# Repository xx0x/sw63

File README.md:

# Space Watch SW63

Sci-fi inspired electronic watch.

*MK4 in the development, out in 2026.*

## How to tell the time?

When the button is briefly pressed, SW63 tells you the time using a sequence of LED blinks. It's not a binary clock, it's inspired by the analog clock hands movement and uses quarters, halves and so on; similar to how people used to tell the time before the digital clock became popular.
  
**16:35**  
*half past - four - hours - and - five - minutes - PM*

**6:57**  
*three - minutes - to - whole - seven - hours*

Language can be changed in the watch menu to reflect the different ways different languages express the time ("half past five" in English is "half of six" in German etc).

See [LANGUAGES.md](./LANGUAGES.md) for the full list and examples.

## Controls

**Short press:** Show the time  
**Long press:** Enter Menu (setting the language and time)  
**Extra long press:** Enter Secret settings  
**Multiple short presses:** Show animation

*In Menu / Secret settings:*  
**Short press:** Change  
**Long press:** Confirm and go to next

## BOM (DIY Kits)

| Name                                | Part Number                                   | Qty |
| ----------------------------------- | --------------------------------------------- | --- |
| PCB with assembled SMD components   | custom part                                   | 1   |
| Red 5 mm LED                        | LL-503VD2E-V1-4D                              | 1   |
| Green 5 mm LED                      | LL-504PGD2E-G5-2B                             | 1   |
| Blue 5 mm LED                       | LL-504BD2E-B4-2B                              | 1   |
| Yellow 5 mm LED                     | N0Y64L35<br> L-53SYD<br> L-53SYDK             | 1   |
| Yellow 3×2 mm LED                   | LL-234YD2Q-1B                                 | 4   |
| Red 3 mm LED                        | FYL-3014LRD1A<br> FYL-3014SRT1A               | 1   |
| Li-Po battery LP301020 or LP301120* | AKY0471<br> SparkFun 13852<br> SparkFun 25270 | 1   |
| CNC aluminium enclosure             | custom part                                   | 1   |
| Screw M1.6 length 4mm (hex socket)  | -                                             | 4   |
| 18 mm watch spring bar              | -                                             | 2   |
| 18 mm watch strap                   | -                                             | 1   |

> [!WARNING]
> \***Note:** Due to the shipping restrictions the Li-Po battery isn't part of the DIY Kit. Please provide your own 40 mAh battery with dimensions 20 mm × 11 mm × 3 mm (or smaller) with the integrated protection circuit.

## License

**Schematics, Hardware Designs**  
CERN-OHL-P-2.0

**Code**  
MIT

**Visual elements, Graphics, Documentation**  
CC BY-SA 4.0

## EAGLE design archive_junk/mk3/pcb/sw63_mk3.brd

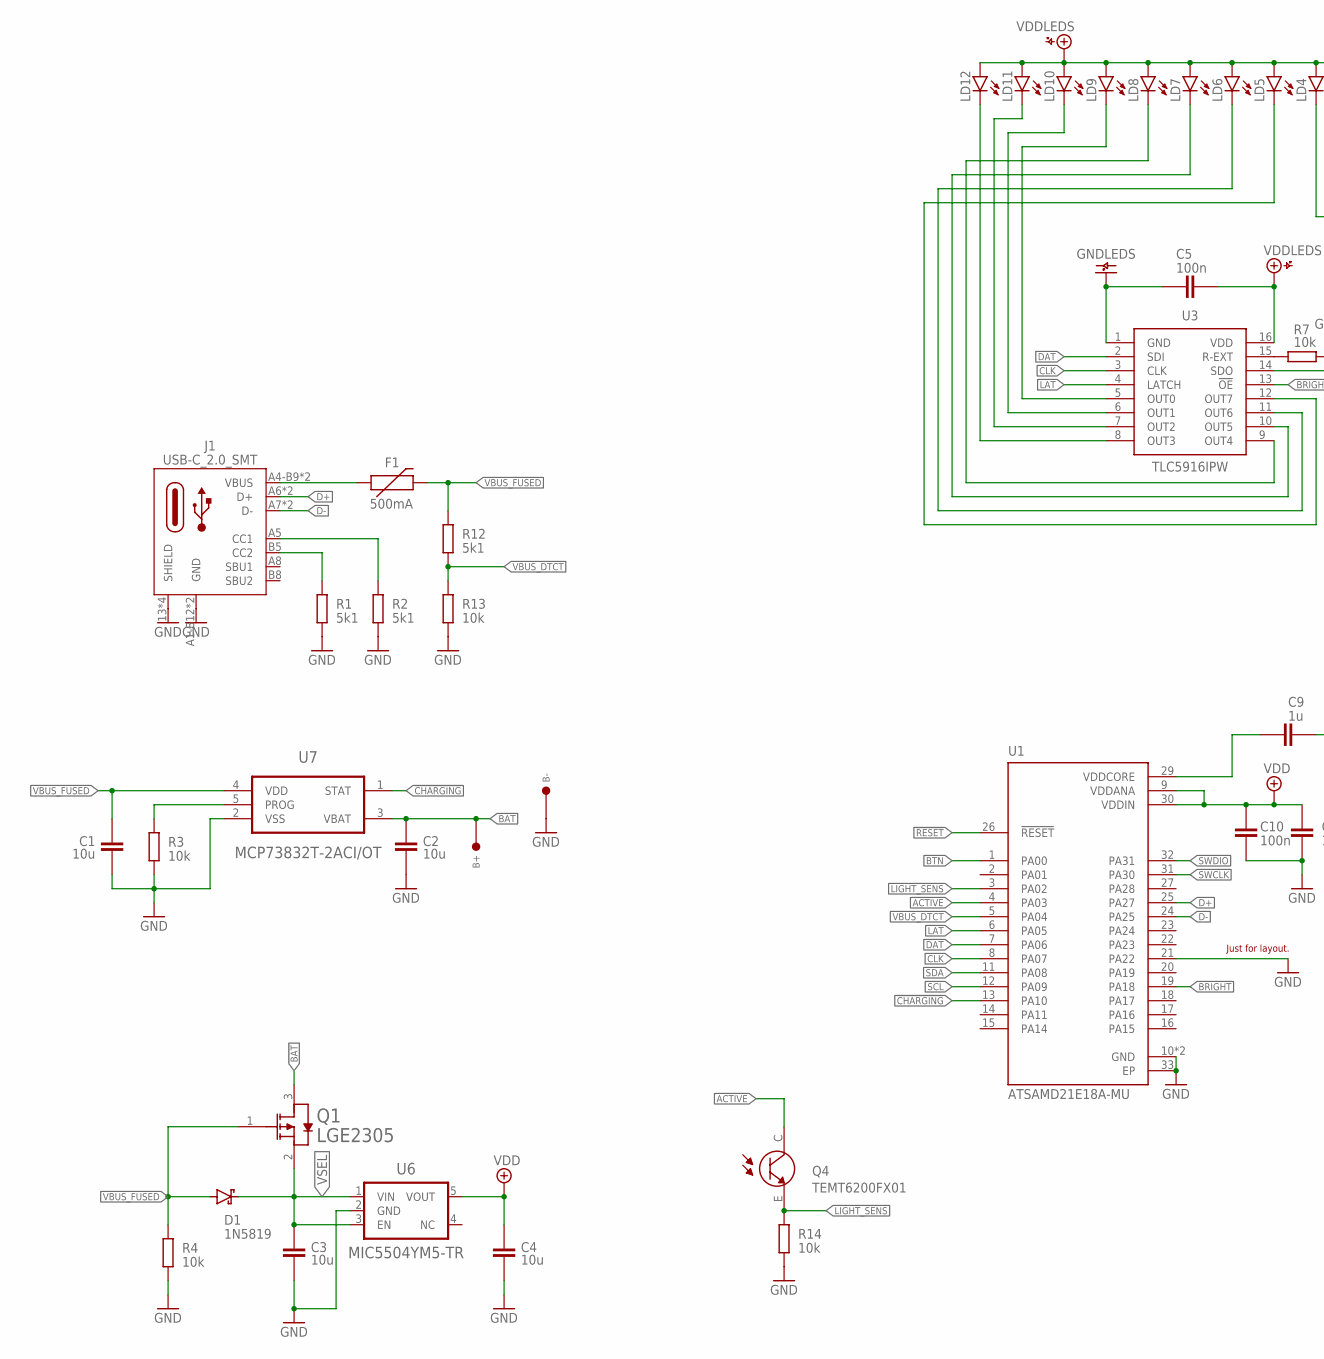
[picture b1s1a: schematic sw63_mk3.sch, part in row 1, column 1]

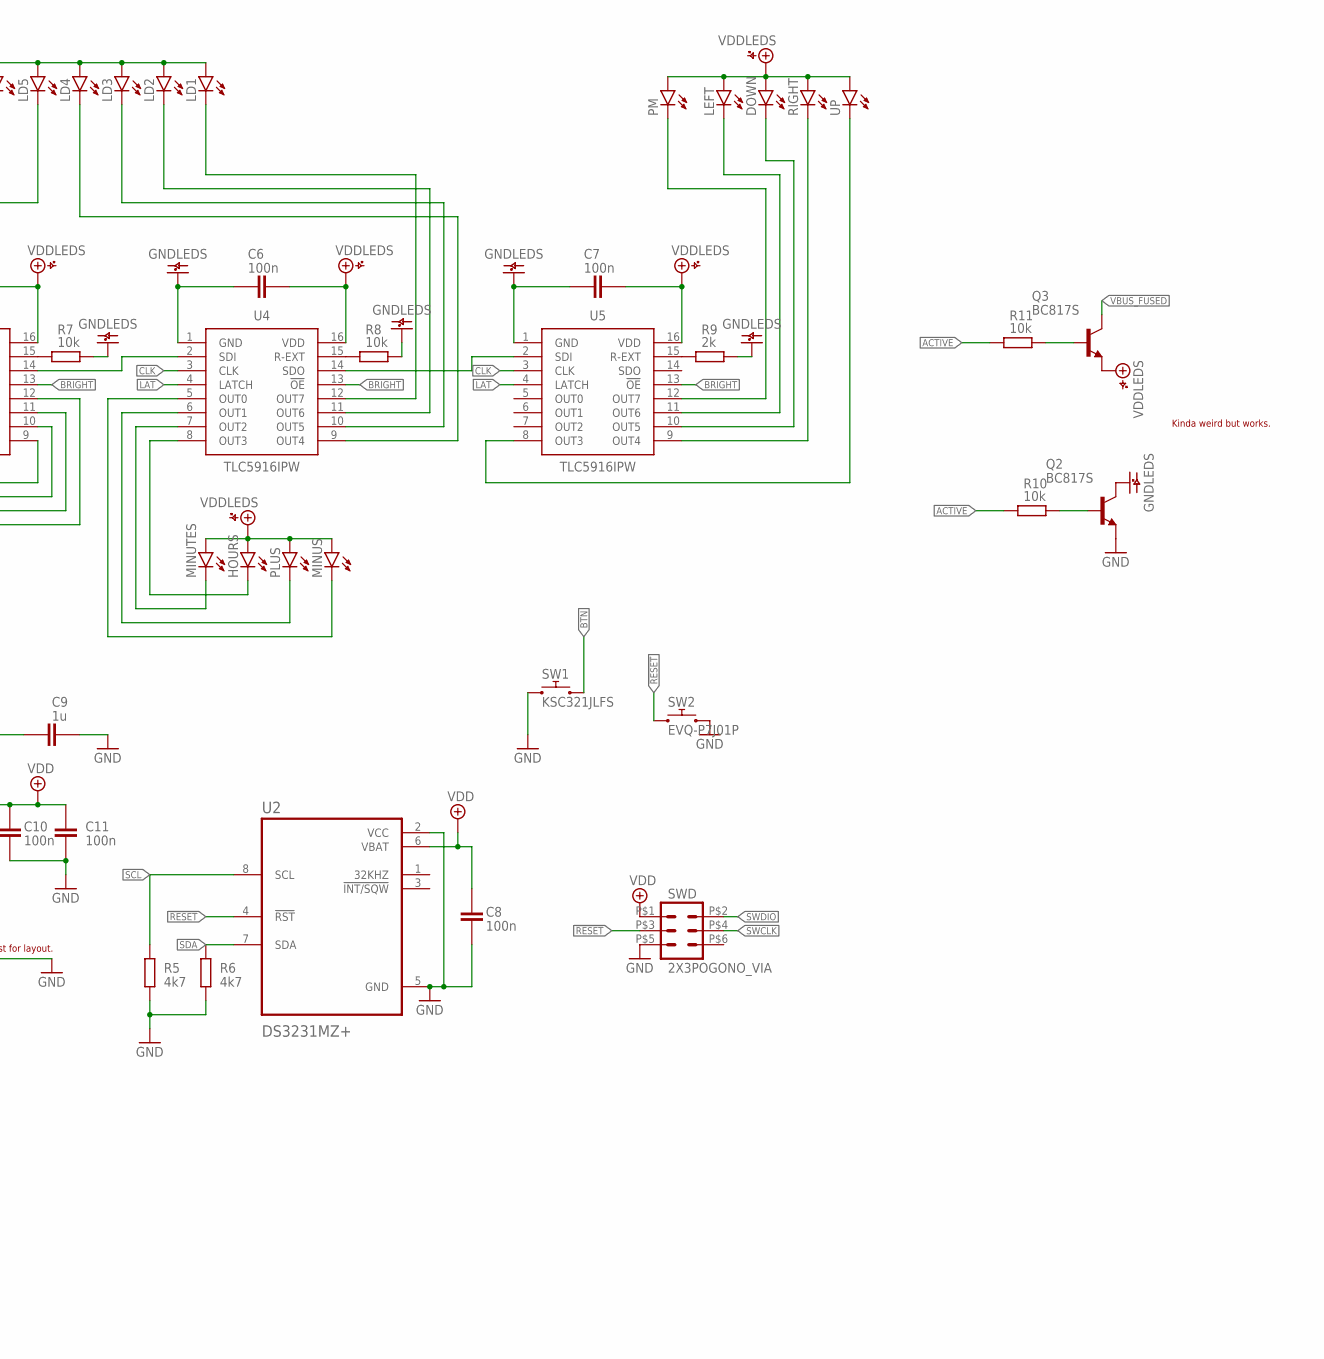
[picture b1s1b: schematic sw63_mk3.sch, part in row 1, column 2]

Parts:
B+: TEST_PIN_LARGE; TEST_PIN_2.0
B-: TEST_PIN_LARGE; TEST_PIN_2.0
C1, C2, C3, C4: 10u; CAPACITOR0805
C5, C6, C7, C8, C10, C11: 100n; CAPACITOR0603
C9: 1u; CAPACITOR0603
D1: 1N5819; SOD123
DOWN: LED_RECT-3.2X2; LED_RECT_3.2X2
F1: 500mA; PTC0805
HOURS: LED_THT-5MM_B; LED_5MM_BLUE
J1: USB-C_2.0_SMT; USB-C_FULL_SMT
LD1, LD2, LD3, LD4, LD5, LD6, LD7, LD8, LD9, LD10, LD11, LD12: LED_SMT_1206; LED_1206
LEFT: LED_RECT-3.2X2; LED_RECT_3.2X2
MINUS: LED_THT-5MM_R; LED_5MM_RED
MINUTES: LED_THT-5MM_Y; LED_5MM_YELLOW
PLUS: LED_THT-5MM_G; LED_5MM_GREEN
PM: LED_THT-3MM_ALT; LED_3MM_ALT
Q1: LGE2305; SOT23
Q2, Q3: BC817S; SOT23
Q4: TEMT6200FX01
R1, R2, R12: 5k1; RESISTOR0603
R3, R4, R7, R8, R10, R11, R13, R14: 10k; RESISTOR0603
R5, R6: 4k7; RESISTOR0603
R9: 2k; RESISTOR0603
RIGHT: LED_RECT-3.2X2; LED_RECT_3.2X2
SW1: KSC321JLFS; KSC3XXJ
SW2: EVQ-P7J01P
SWD: 2X3POGONO_VIA; 2X3_POGO_NO_VIA
U1: ATSAMD21E18A-MU; QFN50P500X500X100-33N
U2: DS3231MZ+; SO8
U3, U4, U5: TLC5916IPW; TSSOP16
U6: MIC5504YM5-TR; SOT23-5
U7: MCP73832T-2ACI/OT; SOT23-5
UP: LED_RECT-3.2X2; LED_RECT_3.2X2

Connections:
!CHARGING: U1.13 (PA10), U7.1 (STAT)
!RESET: SW2.1_1 (1), SW2.1_2 (1), SWD.P$3 (3), U1.26 (!RESET), U2.4 (!RST)
ACTIVE: Q4.C, R10.2, R11.2, U1.4 (PA03)
BAT: B+.P$1, C2.1, Q1.3 (DRAIN), U7.3 (VBAT)
BRIGHT: U1.19 (PA18), U3.13 (!OE), U4.13 (!OE), U5.13 (!OE)
BTN: SW1.2, SW1.4 (2), U1.1 (PA00)
CLK: U1.8 (PA07), U3.3 (CLK), U4.3 (CLK), U5.3 (CLK)
D+: J1.A6 (D+), J1.B6 (D+), U1.25 (PA27)
D-: J1.A7 (D-), J1.B7 (D-), U1.24 (PA25)
DAT: U1.7 (PA06), U3.2 (SDI)
GND: B-.P$1, C1.2, C2.2, C3.2, C4.2, C8.2, C9.1, C10.1, C11.1, J1.13 (SHIELD), J1.14 (SHIELD), J1.15 (SHIELD), J1.16 (SHIELD), J1.A1-B12 (GND), J1.B1-A12 (GND), Q2.2 (E), R1.1, R2.1, R3.1, R4.1, R5.1, R6.1, R13.1, R14.1, SW1.1, SW1.3 (1), SW2.2_1 (2), SW2.2_2 (2), SWD.P$5 (5), U1.10 (GND), U1.21 (PA22), U1.28 (GND), U1.33 (EP), U2.2 (VCC), U2.5 (GND), U6.2 (GND), U7.2 (VSS)
GNDLEDS: C5.1, C6.1, C7.1, Q2.3 (C), R7.1, R8.1, R9.1, U3.1 (GND), U4.1 (GND), U5.1 (GND)
LAT: U1.6 (PA05), U3.4 (LATCH), U4.4 (LATCH), U5.4 (LATCH)
LIGHT_SENS: Q4.E, R14.2, U1.3 (PA02)
unnamed: F1.2 (1), J1.A4-B9 (VBUS), J1.B4-A9 (VBUS)
unnamed: J1.B5 (CC2), R1.2
unnamed: J1.A5 (CC1), R2.2
unnamed: R3.2, U7.5 (PROG)
unnamed: LD12.C, U3.8 (OUT3)
unnamed: LD11.C, U3.7 (OUT2)
unnamed: R7.2, U3.15 (R-EXT)
unnamed: R8.2, U4.15 (R-EXT)
unnamed: R9.2, U5.15 (R-EXT)
unnamed: Q2.1 (B), R10.1
unnamed: U4.14 (SDO), U5.2 (SDI)
unnamed: U3.14 (SDO), U4.2 (SDI)
unnamed: Q3.1 (B), R11.1
unnamed: PM.K (C), U5.12 (OUT7)
unnamed: DOWN.K (C), U5.10 (OUT5)
unnamed: LEFT.K (C), U5.11 (OUT6)
unnamed: RIGHT.K (C), U5.9 (OUT4)
unnamed: U5.8 (OUT3), UP.K (C)
unnamed: LD10.C, U3.6 (OUT1)
unnamed: LD9.C, U3.5 (OUT0)
unnamed: LD8.C, U3.9 (OUT4)
unnamed: LD7.C, U3.10 (OUT5)
unnamed: LD6.C, U3.11 (OUT6)
unnamed: LD5.C, U3.12 (OUT7)
unnamed: C9.2, U1.29 (VDDCORE)
unnamed: LD4.C, U4.9 (OUT4)
unnamed: LD3.C, U4.10 (OUT5)
unnamed: LD2.C, U4.11 (OUT6)
unnamed: LD1.C, U4.12 (OUT7)
unnamed: HOURS.K (C), U4.8 (OUT3)
unnamed: MINUTES.K (C), U4.7 (OUT2)
unnamed: PLUS.K (C), U4.6 (OUT1)
unnamed: MINUS.K (C), U4.5 (OUT0)
SCL: R5.2, U1.12 (PA09), U2.8 (SCL)
SDA: R6.2, U1.11 (PA08), U2.7 (SDA)
SWCLK: SWD.P$4 (4), U1.31 (PA30)
SWDIO: SWD.P$2 (2), U1.32 (PA31)
VBUS_DTCT: R12.1, R13.2, U1.5 (PA04)
VBUS_FUSED: C1.1, D1.A, F1.3 (2), Q1.1 (GATE), Q3.3 (C), R4.2, R12.2, U7.4 (VDD)
VDD: C4.1, C8.1, C10.2, C11.2, SWD.P$1 (1), U1.9 (VDDANA), U1.30 (VDDIN), U2.6 (VBAT), U6.5 (VOUT)
VDDLEDS: C5.2, C6.2, C7.2, DOWN.A, HOURS.A, LD1.A, LD2.A, LD3.A, LD4.A, LD5.A, LD6.A, LD7.A, LD8.A, LD9.A, LD10.A, LD11.A, LD12.A, LEFT.A, MINUS.A, MINUTES.A, PLUS.A, PM.A, Q3.2 (E), RIGHT.A, U3.16 (VDD), U4.16 (VDD), U5.16 (VDD), UP.A
VSEL: C3.1, D1.C, Q1.2 (SOURCE), U6.1 (VIN), U6.3 (EN)

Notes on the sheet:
Kinda weird but works.
Just for layout.

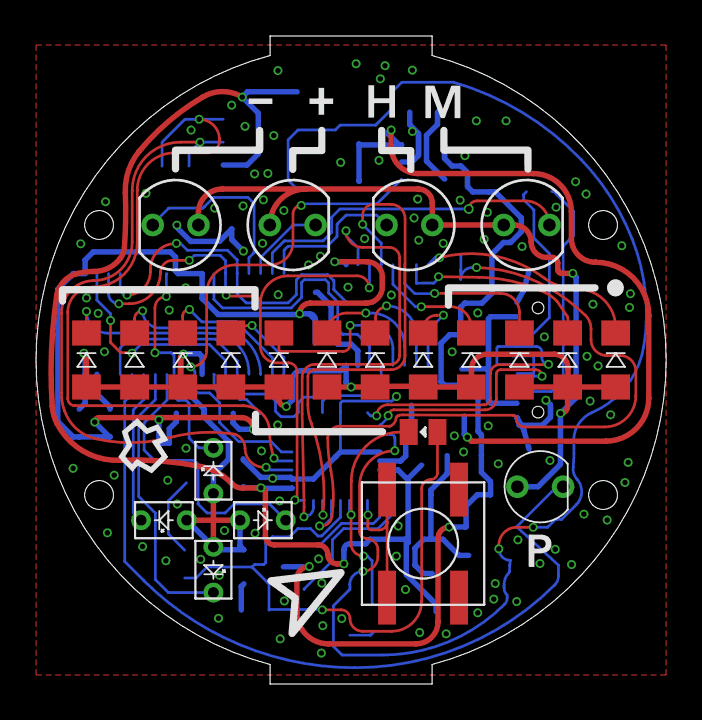
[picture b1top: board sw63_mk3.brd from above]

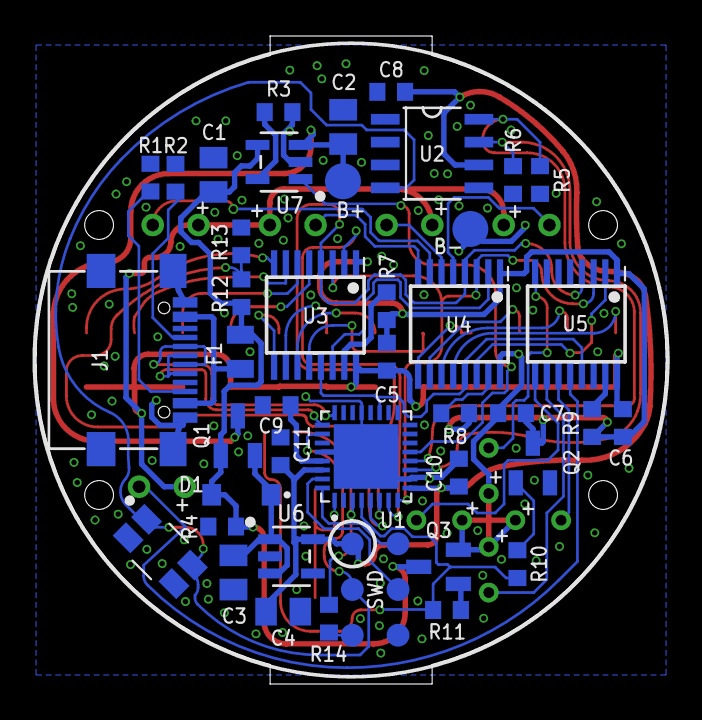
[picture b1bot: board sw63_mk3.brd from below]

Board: 2 copper layers, 35.0 x 36.0 mm, 65 parts (42 on the bottom side), 56 nets.

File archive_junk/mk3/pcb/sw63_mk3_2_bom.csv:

Comment,Designator,Footprint,LCSC Part #
,PM,LED_3MM_ALT,
,HOURS,LED_5MM_BLUE,
,PLUS,LED_5MM_GREEN,
,MINUS,LED_5MM_RED,
,MINUTES,LED_5MM_YELLOW,
1N5819,D1,SOD123,
1u,C9,CAPACITOR0603,
2X3POGONO_VIA,SWD,2X3_POGO_NO_VIA,
2k,R9,RESISTOR0603,
4k7,R5 R6,RESISTOR0603,
5k1,R1 R2 R12,RESISTOR0603,
10k,R3 R4 R7 R8 R10 R13 R14,RESISTOR0603,
10u,C1 C2 C3 C4,CAPACITOR0805,
100n,C5 C6 C7 C8 C10 C11,CAPACITOR0603,
2302,Q2,SOT23,
2305,Q1,SOT23,
ATSAMD21E18A-MU,U1,QFN50P500X500X100-33N,
BSMD0805-050-24V,F1,PTC0805,
DS3231MZ+,U2,SO8,
GT-USB-7070C,J1,USB-C_FULL_SMT_WS,
KSC321JLFS,SW1,KSC3XXJ,
LED_RECT-3.2X2,DOWN LEFT RIGHT UP,LED_RECT_3.2X2,
LED_SMT_1206,LD1 LD2 LD3 LD4 LD5 LD6 LD7 LD8 LD9 LD10 LD11 LD12,LED_1206,
MCP73832T-2ACI/OT,U7,SOT23-5,
ME6211C33M5G-N,U6,SOT23-5,
RB521S,D2 D3 D4 D5,SOD523,
SMALL_NC,SJ1,SMALL_NC_NOSILK,
TEMT6200FX01,Q4,TEMT6200FX01,
TEST_PIN_LARGE,B+ B-,TEST_PIN_2.0,
TLC5916IPW,U3 U4 U5,TSSOP16,
TSC4A 160gf-WZ 016,SW2,EVQ-P7J01P,

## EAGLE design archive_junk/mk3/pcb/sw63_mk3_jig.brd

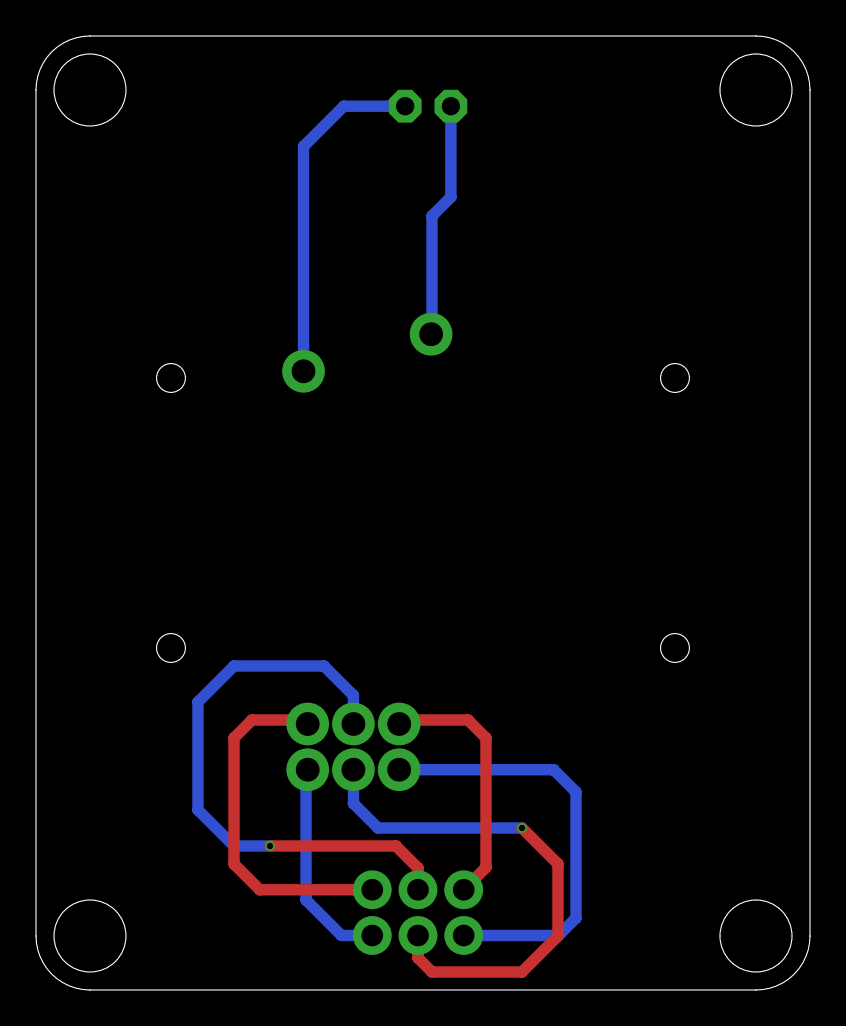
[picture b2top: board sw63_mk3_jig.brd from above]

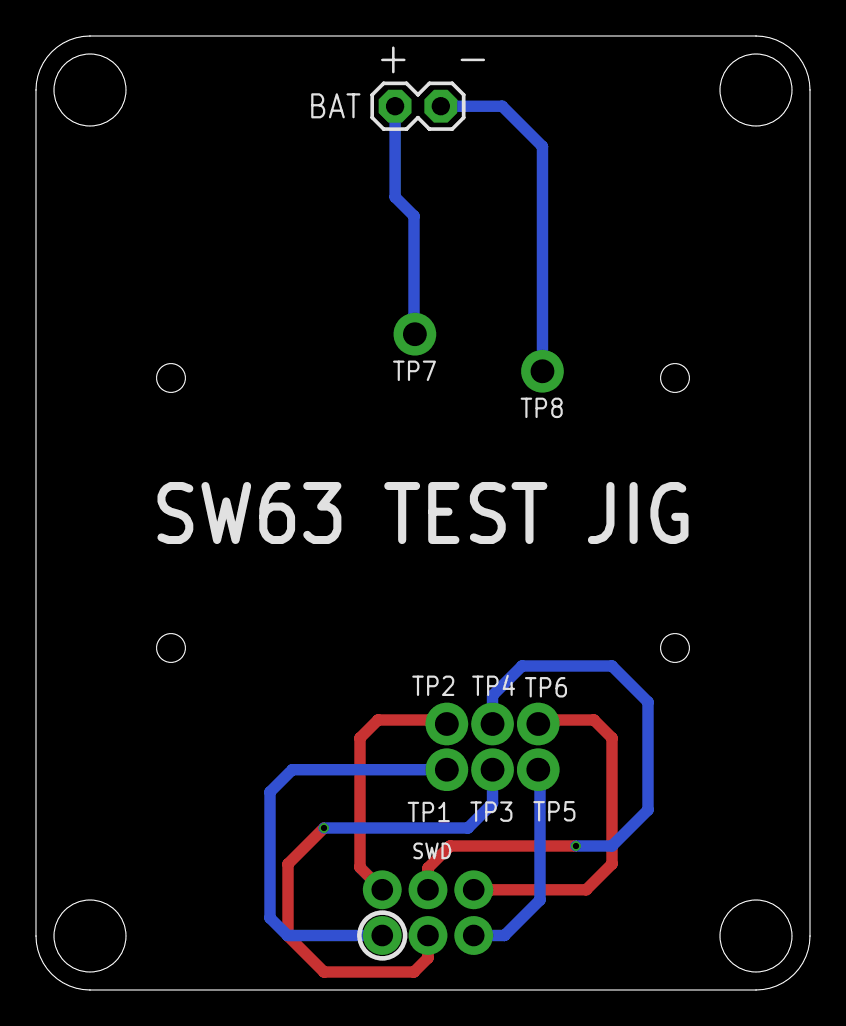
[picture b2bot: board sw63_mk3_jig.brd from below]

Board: 2 copper layers, 43.0 x 53.0 mm, 10 parts (10 on the bottom side), 8 nets.

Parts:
BAT: M02PTH; 1X02
SWD: 2X3_POGO_ROUND
TP1, TP2, TP3, TP4, TP5, TP6, TP7, TP8: R-075-SC; R-075

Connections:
BAT+: BAT.1, TP7.P$1
BAT-: BAT.2, TP8.P$1
unnamed: SWD.P$1, TP1.P$1
unnamed: SWD.P$3, TP3.P$1
unnamed: SWD.P$5, TP5.P$1
unnamed: SWD.P$6, TP6.P$1
unnamed: SWD.P$4, TP4.P$1
unnamed: SWD.P$2, TP2.P$1

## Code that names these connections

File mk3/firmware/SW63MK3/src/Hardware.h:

#ifndef SW63_HARDWARE_H
#define SW63_HARDWARE_H

#include <Arduino.h>
#include "types.h"

namespace SW63
{
    class Hardware
    {
    public:
        enum Pins
        {
            PIN_BTN,
            PIN_UNUSED1,
            PIN_LIGHT_SENS,
            PIN_ACTIVE,
            PIN_VBUS_DTCT,
            PIN_LAT,
            PIN_DAT,
            PIN_CLK,
            PIN_SDA,
            PIN_SCL,
            PIN_CHARGING,
            PIN_UNUSED2,
            PIN_UNUSED3,
            PIN_UNUSED4,
            PIN_UNUSED5,
            PIN_UNUSED6,
            PIN_BRIGHTNESS,
        };

        enum BitPositions
        {
            BP_PM,
            BP_LEFT,
            BP_DOWN,
            BP_RIGHT,
            BP_UP,
            BP_UNUSED2,
            BP_UNUSED1,
            BP_UNUSED0,
            BP_12,
            BP_11,
            BP_10,
            BP_9,
            BP_HOURS,
            BP_MINUTES,
            BP_PLUS,
            BP_MINUS,
            BP_8,
            BP_7,
            BP_6,
            BP_5,
            BP_1,
            BP_2,
            BP_3,
            BP_4,
        };

        void Init(voidFuncPtr button_callback, voidFuncPtr charge_callback);
        void SetLeds(bool minus, bool plus, bool hours, bool minutes, uint32_t digit, ClockFace face, bool pm);
        void ClearLeds();
        void TransferLeds();
        void SetActive(bool active);
        bool GetButtonState();
        void AutoBrightness();
        void Sleep();
        bool IsCharging();
        bool IsChargerConnected();

    private:
        uint32_t led_buffer_ = 0;
        void InitPins(bool init_interrupts);
        void SetBrightness(uint8_t brightness);
        uint16_t GetLightSensorValue();
    };

}

#endif

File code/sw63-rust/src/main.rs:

#![no_std]
#![no_main]

mod ds3231;

use atsamd_hal::{
    adc::{Adc, Gain, Reference, Resolution, SampleRate},
    clock::GenericClockController,
    delay::Delay,
    gpio::v2::{Pins, B, C},
    pac::{interrupt, CorePeripherals, EIC, GCLK, NVIC},
    prelude::*,
    sercom::i2c,
    target_device::Peripherals,
    time::U32Ext,
};

use cortex_m_rt::entry;
use panic_halt as _;

use ds3231::{Time, DS3231};

#[entry]
fn main() -> ! {
    // Get peripherals
    let mut peripherals = Peripherals::take().unwrap();
    let mut core = CorePeripherals::take().unwrap();

    // Configure clocks using the internal oscillator
    let mut clocks = GenericClockController::with_internal_32kosc(
        peripherals.GCLK,
        &mut peripherals.PM,
        &mut peripherals.SYSCTRL,
        &mut peripherals.NVMCTRL,
    );

    // Configure pins
    let pins = Pins::new(peripherals.PORT);

    // Configure LED on PA23 and button on PA04
    let mut led_pin = pins.pa23.into_push_pull_output();

    // Setup delay provider
    let mut delay = Delay::new(core.SYST, &mut clocks);

    // Startup indicator
    led_pin.set_high().unwrap();
    delay.delay_ms(200u32);
    led_pin.set_low().unwrap();

    // ==================================================
    // Configure GCLK with minimal power for EIC operation
    // ==================================================

    let gclk = unsafe { &*GCLK::ptr() };

    // Configure GCLK1 to use OSC32K with minimal power
    unsafe {
        // First disable the clock generator
        gclk.genctrl.write(|w| w.id().bits(1).genen().clear_bit());
        while gclk.status.read().syncbusy().bit() {}

        // Set division factor to 32 (lower power)
        gclk.gendiv.write(|w| w.id().bits(1).div().bits(32));
        while gclk.status.read().syncbusy().bit() {}

        // Configure with OSC32K and enable in standby
        gclk.genctrl.write(|w| {
            w.id().bits(1)
             .src().osc32k()
             .idc().clear_bit()    // Disable improved duty cycle (lower power)
             .genen().set_bit()
             .runstdby().set_bit() // Must run in standby for wakeup to work
        });
        while gclk.status.read().syncbusy().bit() {}

        // Connect GCLK1 to the EIC
        gclk.clkctrl.write(|w| {
            w.id().eic()
             .gen().bits(1)
             .clken().set_bit()
        });
        while gclk.status.read().syncbusy().bit() {}
    }

    // Enable EIC peripheral clock
    peripherals.PM.apbamask.modify(|_, w| w.eic_().set_bit());

    // Get EIC access
    let eic = &peripherals.EIC;

    // Disable EIC before configuring
    eic.ctrl.write(|w| w.enable().clear_bit());
    while eic.status.read().syncbusy().bit_is_set() {}

    // Configure only the button interrupt (PA04 = EXTINT[4])
    // Use input filtering to avoid spurious wakeups
    eic.config[0].write(|w| w.sense4().fall().filten4().set_bit());

    // Only enable the one interrupt we need
    eic.intenset.write(|w| w.extint4().set_bit());

    // Only enable wakeup for the specific interrupt
    eic.wakeup.write(|w| w.wakeupen4().set_bit());

    // Enable EIC
    eic.ctrl.write(|w| w.enable().set_bit());
    while eic.status.read().syncbusy().bit_is_set() {}

    // Clear any pending interrupt
    eic.intflag.write(|w| w.extint4().set_bit());

    // Configure button pin for interrupt mode
    let button_pin = pins.pa04.into_pull_up_interrupt();

    // Set up deep sleep mode
    core.SCB.set_sleepdeep();

    // Enable the EIC interrupt in NVIC
    unsafe {
        NVIC::unmask(interrupt::EIC);
    }

    // Configure I2C pins (SDA on PA08, SCL on PA09)
    // For SERCOM0, both PA08 and PA09 need to be in Alternate C mode
    let sda = pins.pa08.into_alternate::<C>();
    let scl = pins.pa09.into_alternate::<C>();

    // Set up I2C for the DS3231 RTC
    let gclk0 = clocks.gclk0();
    let sercom0_core = clocks.sercom0_core(&gclk0).unwrap();
    let i2c = i2c::I2CMaster0::new(
        &sercom0_core,
        100.khz(),
        peripherals.SERCOM0,
        &mut peripherals.PM,
        sda,
        scl,
    );

    // Create DS3231 driver
    let mut rtc = DS3231::new(i2c);

    // Set the date and time to August 18, 2025, 04:20:00
    let time = Time {
        year: 2025,
        month: 8,
        day: 18,
        hour: 4,
        minute: 20,
        second: 0,
    };

    // Set the time on the DS3231
    if let Err(_) = rtc.set_time(&time) {
        // Handle error (just blink rapidly in this example)
        loop {
            led_pin.toggle().unwrap();
            delay.delay_ms(100u32);
        }
    }

    // Configure PA02 as an analog input
    let mut analog_pin = pins.pa02.into_alternate::<B>();

    // ADC
    let mut adc = Adc::adc(peripherals.ADC, &mut peripherals.PM, &mut clocks);
    adc.reference(Reference::INTVCC1); // Internal 1/2 VDDANA reference
    adc.resolution(Resolution::_12BIT); // 12-bit resolution
    adc.samples(SampleRate::_8); // 8 samples
    adc.gain(Gain::DIV2); // 1/2 gain

    // Blink count
    let mut blink_count = 0u32;

    // Main loop
    loop {
        blink_count += 1u32;
        led_pin.toggle().unwrap();

        // Example sensor readings
        let _current_time = rtc.get_time().unwrap();
        let _brightness: u16 = adc.read(&mut analog_pin).unwrap();

        delay.delay_ms(250u32);

        // Enter deep sleep after 8 blinks
        if blink_count >= 8 {
            // Turn LED off before sleep
            led_pin.set_low().unwrap();
            blink_count = 0;

            // Disable all peripherals to save power
            disable_peripherals(&peripherals.PM);

            // Enter sleep loop - wait for any interrupt (eg. button press)
            loop {
                // Enter standby mode (deepest sleep)
                cortex_m::asm::wfi();

                // Check if button is pressed
                if button_pin.is_low().unwrap() {
                    break;
                }
            }

            // Restore peripherals
            enable_peripherals(&peripherals.PM);
        }
    }
}

#[interrupt]
fn EIC() {
    // Clear the interrupt flag in the EIC
    unsafe {
        let eic = &(*EIC::ptr());
        // Clear interrupt for EXTINT4 (button on PA04)
        eic.intflag.modify(|_, w| w.extint4().set_bit());
    }
}

fn disable_peripherals(pm: &atsamd_hal::pac::PM) {
    // AHB bus - shut down almost everything
    pm.ahbmask.write(|w| {
        w.usb_().clear_bit()
         .dmac_().clear_bit()
         .nvmctrl_().set_bit()
         .dsu_().clear_bit()
    });

    // APBA bus - keep only EIC and SYSCTRL
    pm.apbamask.write(|w| {
        w.eic_().set_bit()
         .wdt_().clear_bit()
         .sysctrl_().set_bit()
         .pac0_().clear_bit()
         .pm_().set_bit()
    });

    // APBB bus - keep only PORT
    pm.apbbmask.write(|w| {
        w.usb_().clear_bit()
         .dmac_().clear_bit()
         .nvmctrl_().clear_bit()
         .dsu_().clear_bit()
         .port_().set_bit()
         .pac1_().clear_bit()
    });

    // APBC bus - disable everything
    pm.apbcmask.write(|w| {
        w.adc_().clear_bit()
         .sercom0_().clear_bit()
         .sercom1_().clear_bit()
         .sercom2_().clear_bit()
         .sercom3_().clear_bit()
         .tcc0_().clear_bit()
         .tcc1_().clear_bit()
         .tcc2_().clear_bit()
         .tc3_().clear_bit()
         .tc4_().clear_bit()
         .tc5_().clear_bit()
         .pac2_().clear_bit()
    });
}

fn enable_peripherals(pm: &atsamd_hal::pac::PM) {
    // AHB bus - restore all peripherals
    pm.ahbmask.write(|w| {
        w.usb_().set_bit()
         .dmac_().set_bit()
         .nvmctrl_().set_bit()
         .dsu_().set_bit()
    });

    // APBA bus - restore all peripherals
    pm.apbamask.write(|w| {
        w.eic_().set_bit()
         .wdt_().set_bit()
         .sysctrl_().set_bit()
         .pac0_().set_bit()
         .pm_().set_bit()
    });

    // APBB bus - restore all peripherals
    pm.apbbmask.write(|w| {
        w.usb_().set_bit()
         .dmac_().set_bit()
         .nvmctrl_().set_bit()
         .dsu_().set_bit()
         .port_().set_bit()
         .pac1_().set_bit()
    });

    // APBC bus - restore all peripherals
    pm.apbcmask.write(|w| {
        w.adc_().set_bit()
         .sercom0_().set_bit()
         .sercom1_().set_bit()
         .sercom2_().set_bit()
         .sercom3_().set_bit()
         .tcc0_().set_bit()
         .tcc1_().set_bit()
         .tcc2_().set_bit()
         .tc3_().set_bit()
         .tc4_().set_bit()
         .tc5_().set_bit()
         .pac2_().set_bit()
    });
}

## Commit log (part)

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2019-12-08 initial sw63 commit
2019-12-08 add schematic
2019-12-08 add charger schematic
2019-12-30 add compiled firmware in HEX format
2019-12-30 add build instructions link
2019-12-30 add video presentation link to readme
2020-05-29 add pcb sources and 3d files
2020-05-29 add Czech manual
2020-07-21 brightness update for v2
2020-08-06 add speed, saver, compressed variant, remove French
2020-08-06 speed updates
2020-08-06 timestart at 00:00
2020-08-12 button handling update
2021-06-11 update readme and schematics
2021-06-11 cleanup, remove old files
2024-08-12 add sw63 mk3 initial schematic + layout
2024-08-13 finishing schematics
2024-08-13 routing done
2024-08-13 layout tweaks
2024-08-13 add graphics
2024-08-14 layout changes for better case compatibility
2024-08-14 update led colors to match reality
2024-08-14 final board touches
2024-08-25 board update
2024-09-01 add bottom graphics
2024-09-01 mk3 coding begin
2024-09-01 add sleep
2024-09-01 implementing animations
2024-09-01 time displaying
2024-09-01 schematic notes
2024-09-01 animations update, add charging animation etc.
2024-11-29 3_2 in progress
2024-11-29 3_2 update
2025-01-15 add 3_2 board files
2025-05-04 basic rust code example
2025-05-04 cleanup, button reading
2025-05-04 working ds3231 example
2025-05-04 implement adc reading
2025-05-04 faking deep sleep for now
2025-05-04 button reading using interrupt
2025-05-04 deep sleep (ugly but kinda works)
2025-05-04 cleanup
2026-01-26 archive old stuff
2026-01-26 begin mk4 schematic
2026-01-26 layout in progress
2026-01-26 update gitignore
2026-01-26 update board
2026-01-28 update models and footprints
2026-01-28 routing in progress
2026-01-28 routing
2026-01-28 routing, graphics
2026-01-28 updated models
2026-01-29 add usb dtct
2026-01-29 panelization prepare
2026-01-29 mfg data
2026-01-30 add case graphics
2026-02-02 update case & graphics
2026-02-02 add submodules for code
2026-02-02 add actual submodules
2026-02-02 add .clang-format
2026-02-02 initial MK4 code commit
2026-02-02 end charge animation when charging done
2026-02-02 AnimationRunner handles timings
2026-02-02 add layer and event support
2026-02-02 update layer support
2026-02-02 add Button class
2026-02-02 update button behavior
2026-02-02 update layer stuff
2026-02-02 double tap to run speed 0
2026-02-02 params tweaking
2026-02-06 bug note
2026-02-06 update for new wiring
2026-02-06 working charge animation
2026-02-06 slower brightness pwm to prevent glitches
2026-02-06 do auto brightness always between frames
2026-02-06 remove double press (was too complicated)
2026-02-06 add power detection
2026-02-06 retry rtc init on startup few times
2026-02-06 simplify date/time
2026-02-07 charge animation cleanup
2026-02-07 rename SHORT_PRESS to JUST_PRESSED
2026-02-07 implement JUST_RELEASED
2026-02-07 working time setting
2026-02-07 cleaner time setting
2026-02-07 cleaner time setting 2
2026-02-07 cleaner time setting 3
2026-02-07 added secret menu
2026-02-07 timing tweaks
2026-02-07 fix warnings
2026-02-07 add custom System::Millis() function
2026-02-07 cleanup button
2026-02-07 add timeout for other than LayerNormal
2026-02-07 move animation type into runner
2026-02-07 move AnimationRunner into LayerNormal
2026-02-07 reorganize LayerNormal events
2026-02-07 AnimationIntro followed by DisplayTime
2026-02-07 low battery indication before sleep
2026-02-07 add battery level display to the secret menu
2026-02-07 add uf2 submodule
2026-02-07 add uf2 output to build process
2026-02-07 default time as 00:00:00
2026-02-07 add bootloader and tasks
2026-02-08 move all settings into the Settings class
2026-02-08 visual style settings
2026-02-08 higher overall brightness
2026-02-08 add tinyusb submodule
2026-02-08 vibe coded serial communication
2026-02-08 add DISPLAY_TIME command, add commands to tasks
2026-02-08 invert charge complete blink cycle
2026-02-08 updated bootloader
2026-02-08 rename bootloader readme
2026-02-08 update bootloader readme
2026-02-08 simplify communication and docs
2026-02-17 remove the 2* brightness (was too bright)
2026-02-17 fix LED driver startup glitch (hopefully)
2026-02-17 add linux vscode config
2026-03-07 add v2 pcb with fixed mosfet
2026-03-07 remove v1 pcb
2026-03-07 slightly smaller pcb, better fit in the enclosure
2026-03-12 updated pcb info
2026-03-12 updated production files
2026-03-12 move the python communication into its' own folder
2026-03-12 remove automatic pcb backups from git
2026-03-12 add backups to gitignore
2026-03-12 basic vite + react project
2026-03-12 quick communication app, ugly but works somehow
2026-03-12 separate SW63Client class
2026-03-12 add config options, dynamically loaded
2026-03-12 implement GET_VERSION
2026-03-12 renumber commands
2026-03-12 set the time +15s (same as in python)
2026-03-12 actual ticking time
2026-03-12 app tweaks
2026-03-13 more speed settings
2026-03-13 update usb stuff
2026-03-13 react app description
2026-03-13 add DISPLAY_INTRO message
2026-03-13 cleanup copy paste code
2026-03-13 rename GET_CONFIG_OPTIONS to GET_CONFIG_OPTION_VALUES
2026-03-13 add single option get/set support
2026-03-13 disconnect when not available
2026-03-24 basic com styling
2026-03-24 style updates
2026-03-26 add logo
2026-03-26 style tweaks
2026-03-26 add log
2026-03-26 log autoscroll
2026-03-26 favicon
2026-03-26 Log is a separate component now
2026-03-26 scrollbar styling
2026-03-26 add app language dropdown (doesn't do anything now)
2026-03-26 add cs, en translations
2026-03-26 translating options
2026-03-26 more translations
2026-03-26 translation update
2026-03-26 log tweaks
2026-03-27 change settings order and naming
2026-03-27 add slowest/fastest speed label
2026-03-27 change version to 0.9
2026-03-27 doxygen comments
2026-03-27 main lincense and cleanup
2026-03-27 fix base url
2026-03-27 update sw63 image, add to readme
2026-03-27 rename archive_junk to .archive
2026-03-28 npm audit fix
2026-03-29 ukraninan translation updates
2026-03-29 languages update
2026-03-29 info button next to languages doesn't do anything now
2026-03-29 fix up language sequences for Polish
2026-04-16 update part names and docs
2026-04-16 add bom
2026-04-16 update to Kicad 10
2026-04-16 readme tweaks
2026-04-16 readme tweaks, add languages doc
2026-04-18 add flashing script
2026-04-25 update vscode configs
2026-04-25 update license year and name
2026-04-25 bump version to 0.9.1
2026-04-26 npm audit
2026-04-27 schematic notes and pdf
2026-05-14 add "-NoGui 1" for faster J-Link upload
